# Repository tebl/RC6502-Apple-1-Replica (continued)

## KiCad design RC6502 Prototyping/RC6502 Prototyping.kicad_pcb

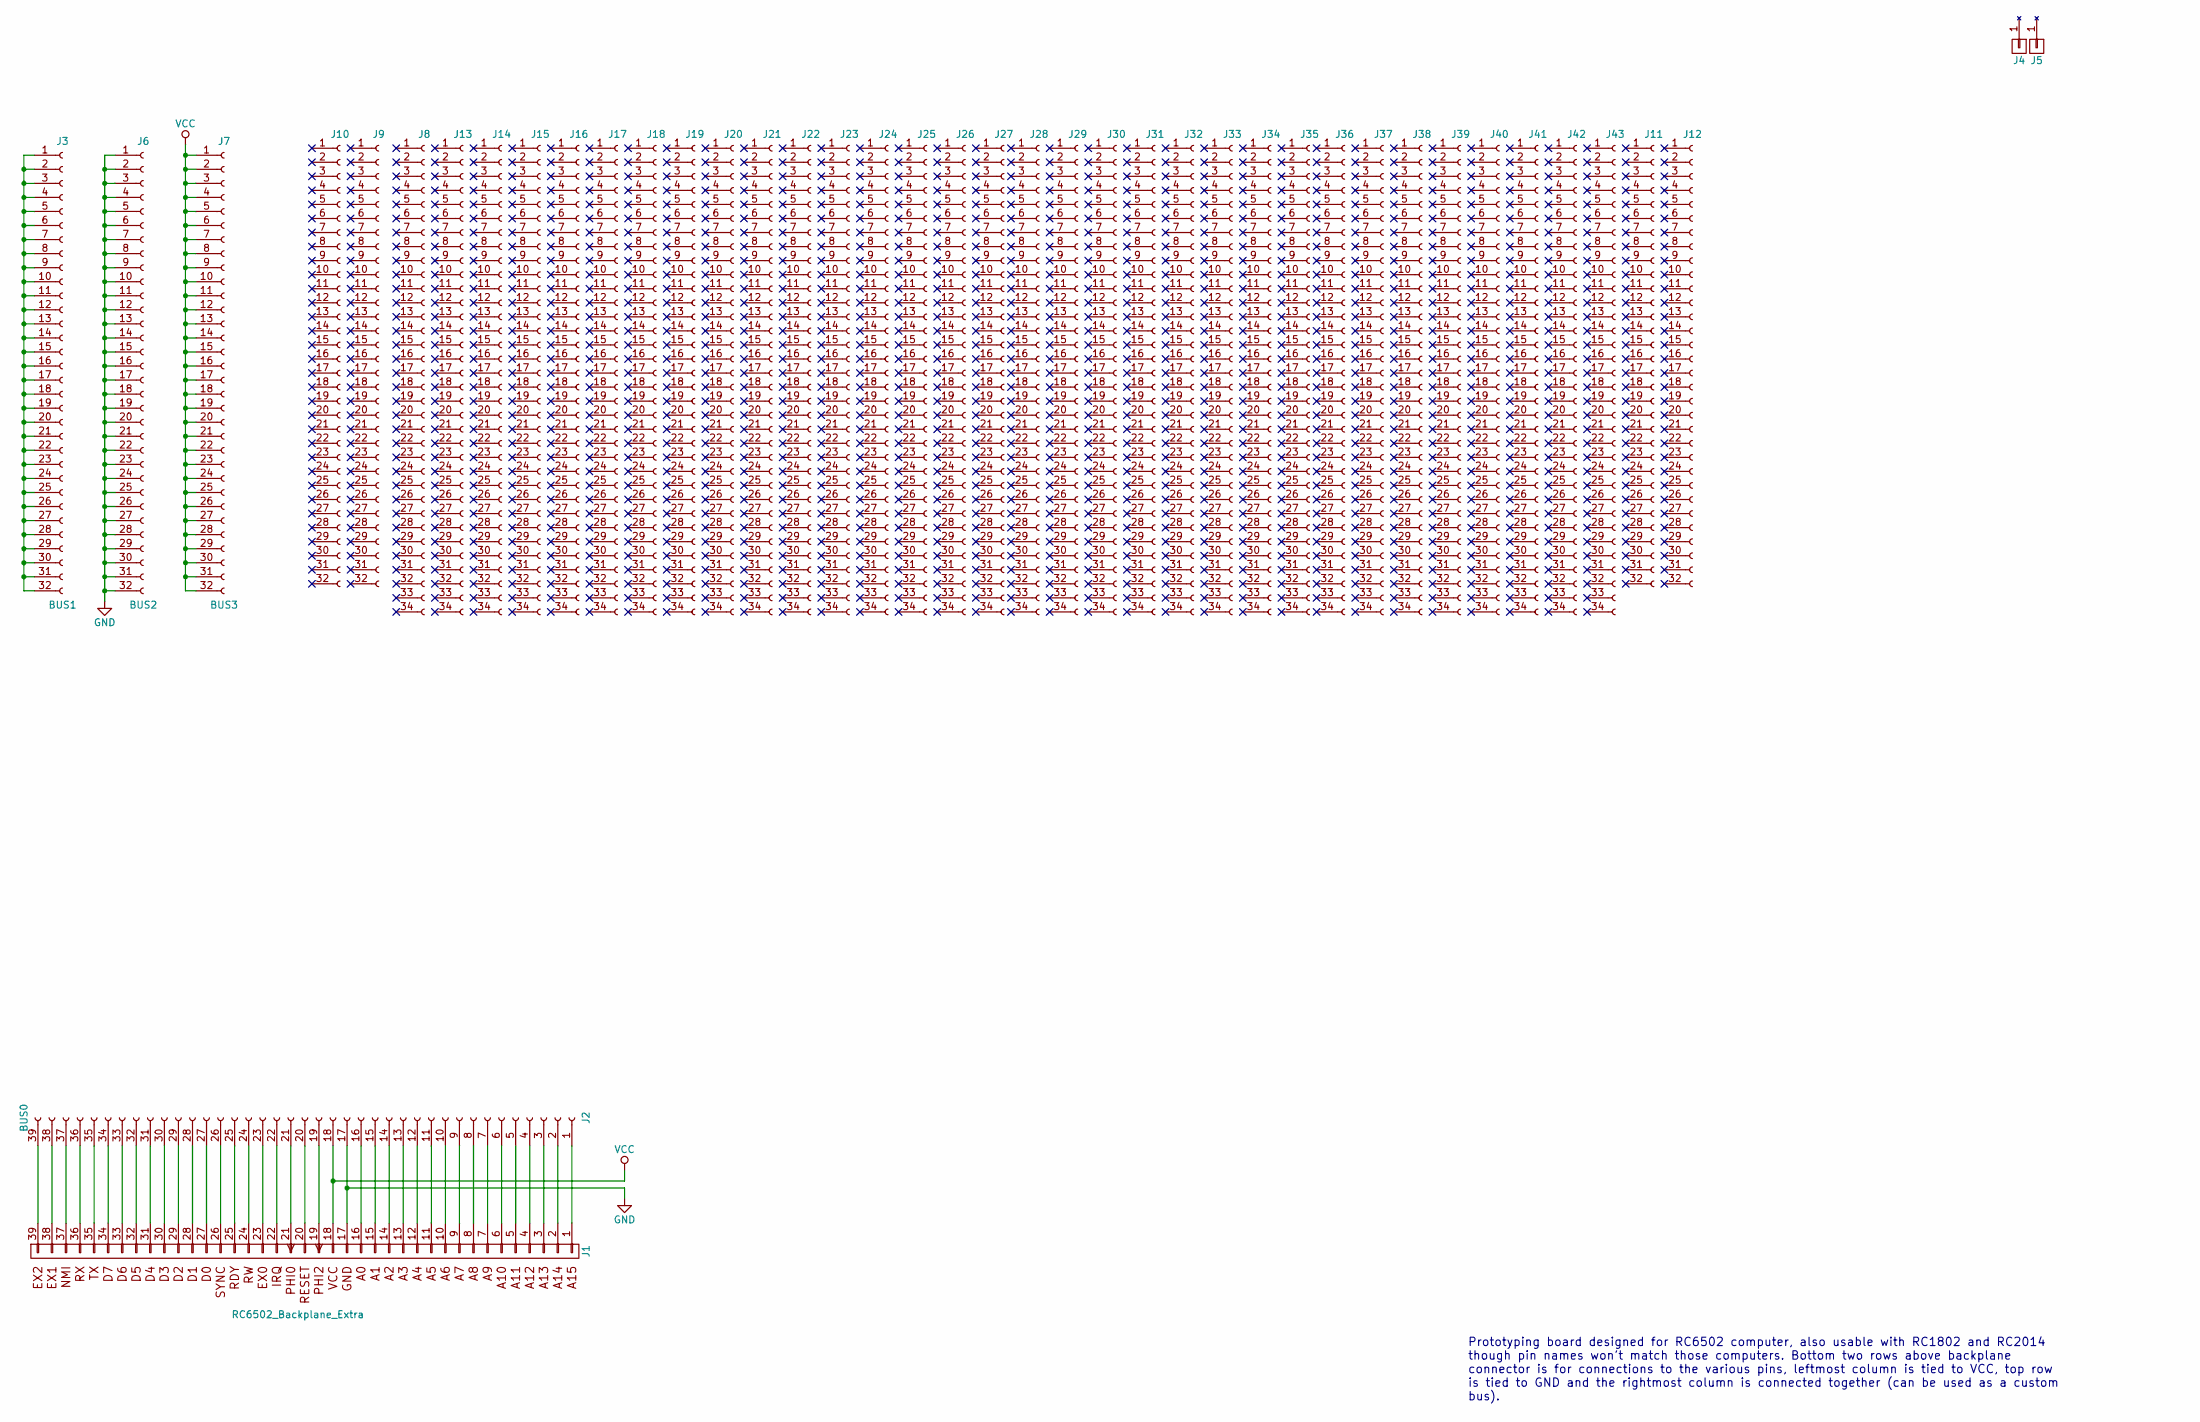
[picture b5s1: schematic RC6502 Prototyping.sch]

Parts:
J1: RC6502_Backplane_Extra; Pin_Header_Angled_1x39_Pitch2.54mm
J2: BUS0; Bus
J3: BUS1; Pin_Header_Straight_1x32_Pitch2.54mm
J4, J5: Mounting
J6: BUS2; Pin_Header_Straight_1x32_Pitch2.54mm
J7: BUS3; Pin_Header_Straight_1x32_Pitch2.54mm
J8, J13, J14, J15, J16, J17, J18, J19, J20, J21, J22, J23, J24, J25, J26, J27, J28, J29, J30, J31, J32, J33, J34, J35, J36, J37, J38, J39, J40, J41, J42, J43: Conn_01x34_Female; 34
J9, J10, J11, J12: Conn_01x32_Female; 32

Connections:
GND: J1.17, J2.17, J6.1, J6.2, J6.3, J6.4, J6.5, J6.6, J6.7, J6.8, J6.9, J6.10, J6.11, J6.12, J6.13, J6.14, J6.15, J6.16, J6.17, J6.18, J6.19, J6.20, J6.21, J6.22, J6.23, J6.24, J6.25, J6.26, J6.27, J6.28, J6.29, J6.30, J6.31, J6.32
unnamed: J1.1 (A15), J2.1
unnamed: J1.2 (A14), J2.2
unnamed: J1.3 (A13), J2.3
unnamed: J1.4 (A12), J2.4
unnamed: J1.5 (A11), J2.5
unnamed: J1.6 (A10), J2.6
unnamed: J1.7 (A9), J2.7
unnamed: J1.8 (A8), J2.8
unnamed: J1.9 (A7), J2.9
unnamed: J1.10 (A6), J2.10
unnamed: J1.11 (A5), J2.11
unnamed: J1.12 (A4), J2.12
unnamed: J1.13 (A3), J2.13
unnamed: J1.14 (A2), J2.14
unnamed: J1.15 (A1), J2.15
unnamed: J1.16 (A0), J2.16
unnamed: J1.19 (PHI2), J2.19
unnamed: J1.20 (RESET), J2.20
unnamed: J1.21 (PHI0), J2.21
unnamed: J1.22 (IRQ), J2.22
unnamed: J1.23 (EX0), J2.23
unnamed: J1.24 (RW), J2.24
unnamed: J1.25 (READY), J2.25
unnamed: J1.26 (SYNC), J2.26
unnamed: J1.27 (D0), J2.27
unnamed: J1.28 (D1), J2.28
unnamed: J1.29 (D2), J2.29
unnamed: J1.30 (D3), J2.30
unnamed: J1.31 (D4), J2.31
unnamed: J1.32 (D5), J2.32
unnamed: J1.33 (D6), J2.33
unnamed: J1.34 (D7), J2.34
unnamed: J1.35 (TX), J2.35
unnamed: J1.36 (RX), J2.36
unnamed: J1.37 (NMI), J2.37
unnamed: J1.38 (EX1), J2.38
unnamed: J1.39 (EX2), J2.39
unnamed: J3.1, J3.2, J3.3, J3.4, J3.5, J3.6, J3.7, J3.8, J3.9, J3.10, J3.11, J3.12, J3.13, J3.14, J3.15, J3.16, J3.17, J3.18, J3.19, J3.20, J3.21, J3.22, J3.23, J3.24, J3.25, J3.26, J3.27, J3.28, J3.29, J3.30, J3.31, J3.32
VCC: J1.18, J2.18, J7.1, J7.2, J7.3, J7.4, J7.5, J7.6, J7.7, J7.8, J7.9, J7.10, J7.11, J7.12, J7.13, J7.14, J7.15, J7.16, J7.17, J7.18, J7.19, J7.20, J7.21, J7.22, J7.23, J7.24, J7.25, J7.26, J7.27, J7.28, J7.29, J7.30, J7.31, J7.32

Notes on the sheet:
Prototyping board designed for RC6502 computer, also usable with RC1802 and RC2014 though pin names won't match those computers. Bottom two rows above backplane connector is for connections to the various pins, leftmost column is tied to VCC, top row is tied to GND and the rightmost column is conne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

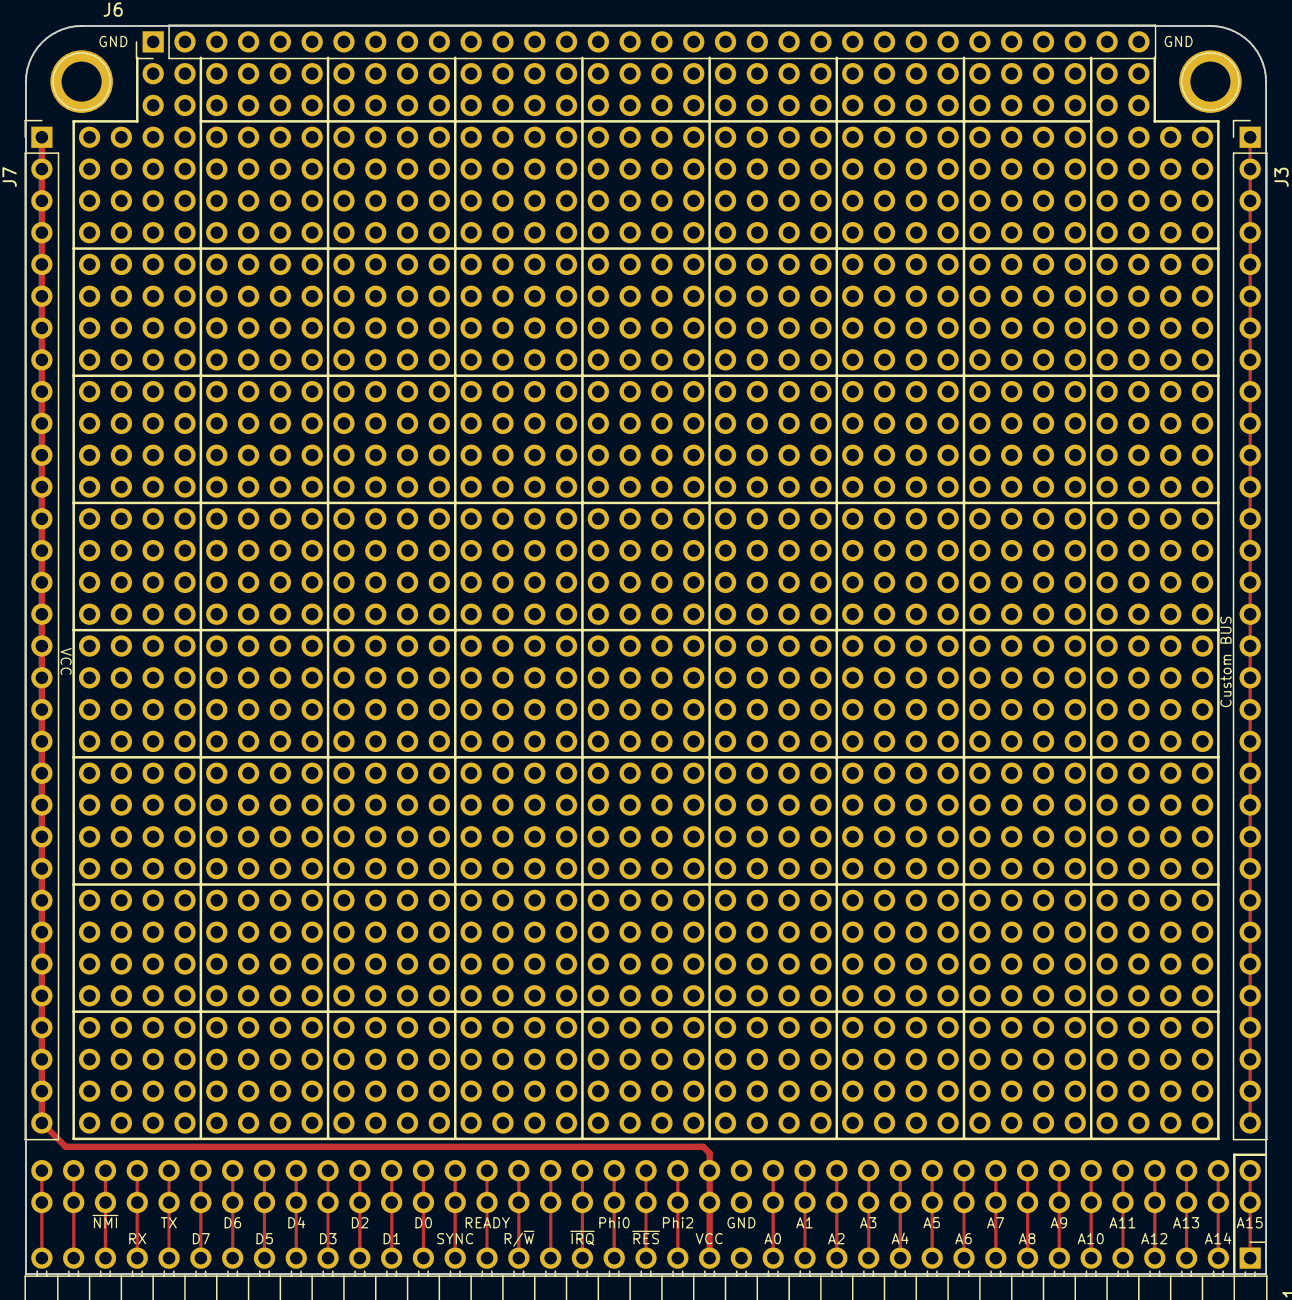
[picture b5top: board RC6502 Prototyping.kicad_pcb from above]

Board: 2 copper layers, 99.1 x 99.7 mm, 43 parts (0 on the bottom side), 40 nets.

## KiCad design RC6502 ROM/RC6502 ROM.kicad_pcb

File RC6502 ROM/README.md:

# RC6502 ROM

The original Apple 1 computer only came with 256 bytes of ROM (Read Only Memory), the bulk of this taken up by the included machine monitor later dubbed WozMon. The machine monitor in itself was written by Wozniak himself by manually entering the data corresponding to the various 6502 instructions and operands byte by byte, mainly because he did not have a computer and the software available to even write assembly level code! An amazing performance by todays standards, though not entirely unheard of in those days since most software was only available for equipment most couldn't even get access to. The Apple 1 was often used with a BASIC variant called "Integer Basic" as a programming language and means of interacting with the machine, but that originally had to be loaded into RAM first via input devices such as tape. The computers original memory map originally looked like the following (picture from Tom Owads Apple 1 Replica book):

.PNG)

The RC6502 computer makes the same changes to the hardware dealing with ROM as was details in the previously mentioned book, the updated memory map looks identical to the one included below (note that any optional modules are not included here). While we initially can see that the blue areas have shifted, this is RAM and we now have an entire 32KB of it as compared to the original - originally we had two blocks of 4KB positioned at the start and at $E000. The modified map changes this second block into ROM, meaning that BASIC is always available to the user, even leaving enough space for at few more utilities!

.PNG)

The implementation of the ROM module answers to addresses from $E000 to $FFFF, in other words the last 8KB of the 6502s 64KB total addressable memory space. The onboard socket takes an EPROM/EEPROM with sizes from 64Kb (27C64/28C64) to 256Kb (27C256/28C256), the latter size giving you the option of using up to four switchable combinations (using A13/14 jumpers). When using the smaller size, these two jumpers should be left unjumpered as the corresponding address pins whould be designated NC (No Connect) on the chips themselves!

**NB!** Note that the redesigned RAM module now supports ROM chips on the same card, so if you do not intend to use the optional paging feature you may want to consider using the new RAM module instead (normally you'd get 5-10 per order anyway)! Note that this might come at an increased cost since the new RAM module requires more ICs to function, but these should be cheap as chips (the potato kind) anyway!

## Optional feature
The board enables the use of backplane pin number 39 for paging purposes, this in essence means the ability to shut of the ROM module using appropriate hardware for controlling this pin. This would enable the computer to regain this section of memory space for other purposes afterwards, possibly by switching it out for more RAM... In most cases this will not be needed, so instead I encourage you to solder a hard links between pads 2 and 3 on JP5 - U2 can also be left off the board.

## Software
As previously mentioned, the supplied binary file (in the [firmware](https://github.com/tebl/RC6502-Apple-1-Replica/tree/master/RC6502%20ROM/firmware)-directory) includes around 8KB of software. The easiest way to get that software onto the selected ROM IC is by using an EPROM programmer, personally I use the MiniPro TL866A and while cheap compared to the alternatives I've found it handles just about anything I've thrown at it.

The following overview is also printed on the back of the SBC silkscreen, while not inherently clear is that the command given is what you would type into the machine monitor program (WozMon) to start the program at the given address. From using the computer and reading the books from the corresponding era you'll want to be spending a lot of your time in BASIC, but when debugging hardware I find WozMon to be the easiest environment to work within. A somewhat detailed guide to the computer can be found by reading the original [operation manual](https://archive.org/details/Apple1Manual1976) from 1976, but the is also a really good guide for the monitor on [https://www.sbprojects.net/projects/apple1/wozmon.php](https://www.sbprojects.net/projects/apple1/wozmon.php).

| Program            | Command |
|--------------------|---------|
| Integer Basic      | $E000 R |
| Krusader Assembler | $F000 R |
| WozMon             | $FF00 R |

# Schematic
The supplied KiCad files should be sufficient as both a schematic and as a starting
point for ordering PCBs, the schematic is also available in
[PDF-format](https://github.com/tebl/RC6502-Apple-1-Replica/raw/master/RC6502%20ROM/export/RC6502%20ROM.pdf). You can refer to the BOM below for a list of suggested components to use, part numbers in parenthesis are optional and is not required.

# BOM
These are the components needed to put together your very own ROM-module for the RC6502 computer, should be able to get all of this from your favourite parts supplier through your favourite local parts supplier. For the pin headers, both male and female - if you can't find the exact pin count, just buy the longer versions and snip/cut off the parts you don't need (get extra in case of accidents, and don't cut yourself either!). Part counts in parenthesis are to be considered optional, so if you don't have any plans for them - then they can probably be left out until you need them.

| Reference | Item                                  | Count  |
| --------- | ------------------------------------- | ------ |
| PCB       | Fabricate yourself using KiCad files  |     1  |
| U1        | 27C64, 28C64, 27C256 or 28C256        |     1  |
| U2        | 74LS00 DIP                            |     1  |
| U3        | 74LS00 DIP                            |   (1)  |
| C1-C3     | 100nF ceramic capacitor               |     3  |
| R1        | 10K Ohm resistor                      |   (1)  |
| J1        | 1x39 right angle pin header, male     |     1  |
| JP1,JP3   | 1x3 straight pin header, male         |     2  |
| JP3,JP4   | 1x3 straight pin header, male         |   (2)  |
| JP5       | Piece of wire                         |     1  |
| JP1,JP3   | 1x3 straight pin header, male         |     1  |
|           | Jumper caps                           | 2 (2)  |

If you would like to have a copy of one or more modules, what you'll need to do is zip up the contents of the export directory for each module and give that to your favourite PCB fabrication plant. Personally I prefer to use [PCBWay](https://www.pcbway.com/setinvite.aspx?inviteid=88707), each module has been designed to fit inside the 5$ dimensions. Use the link provided when signing up to support this project!

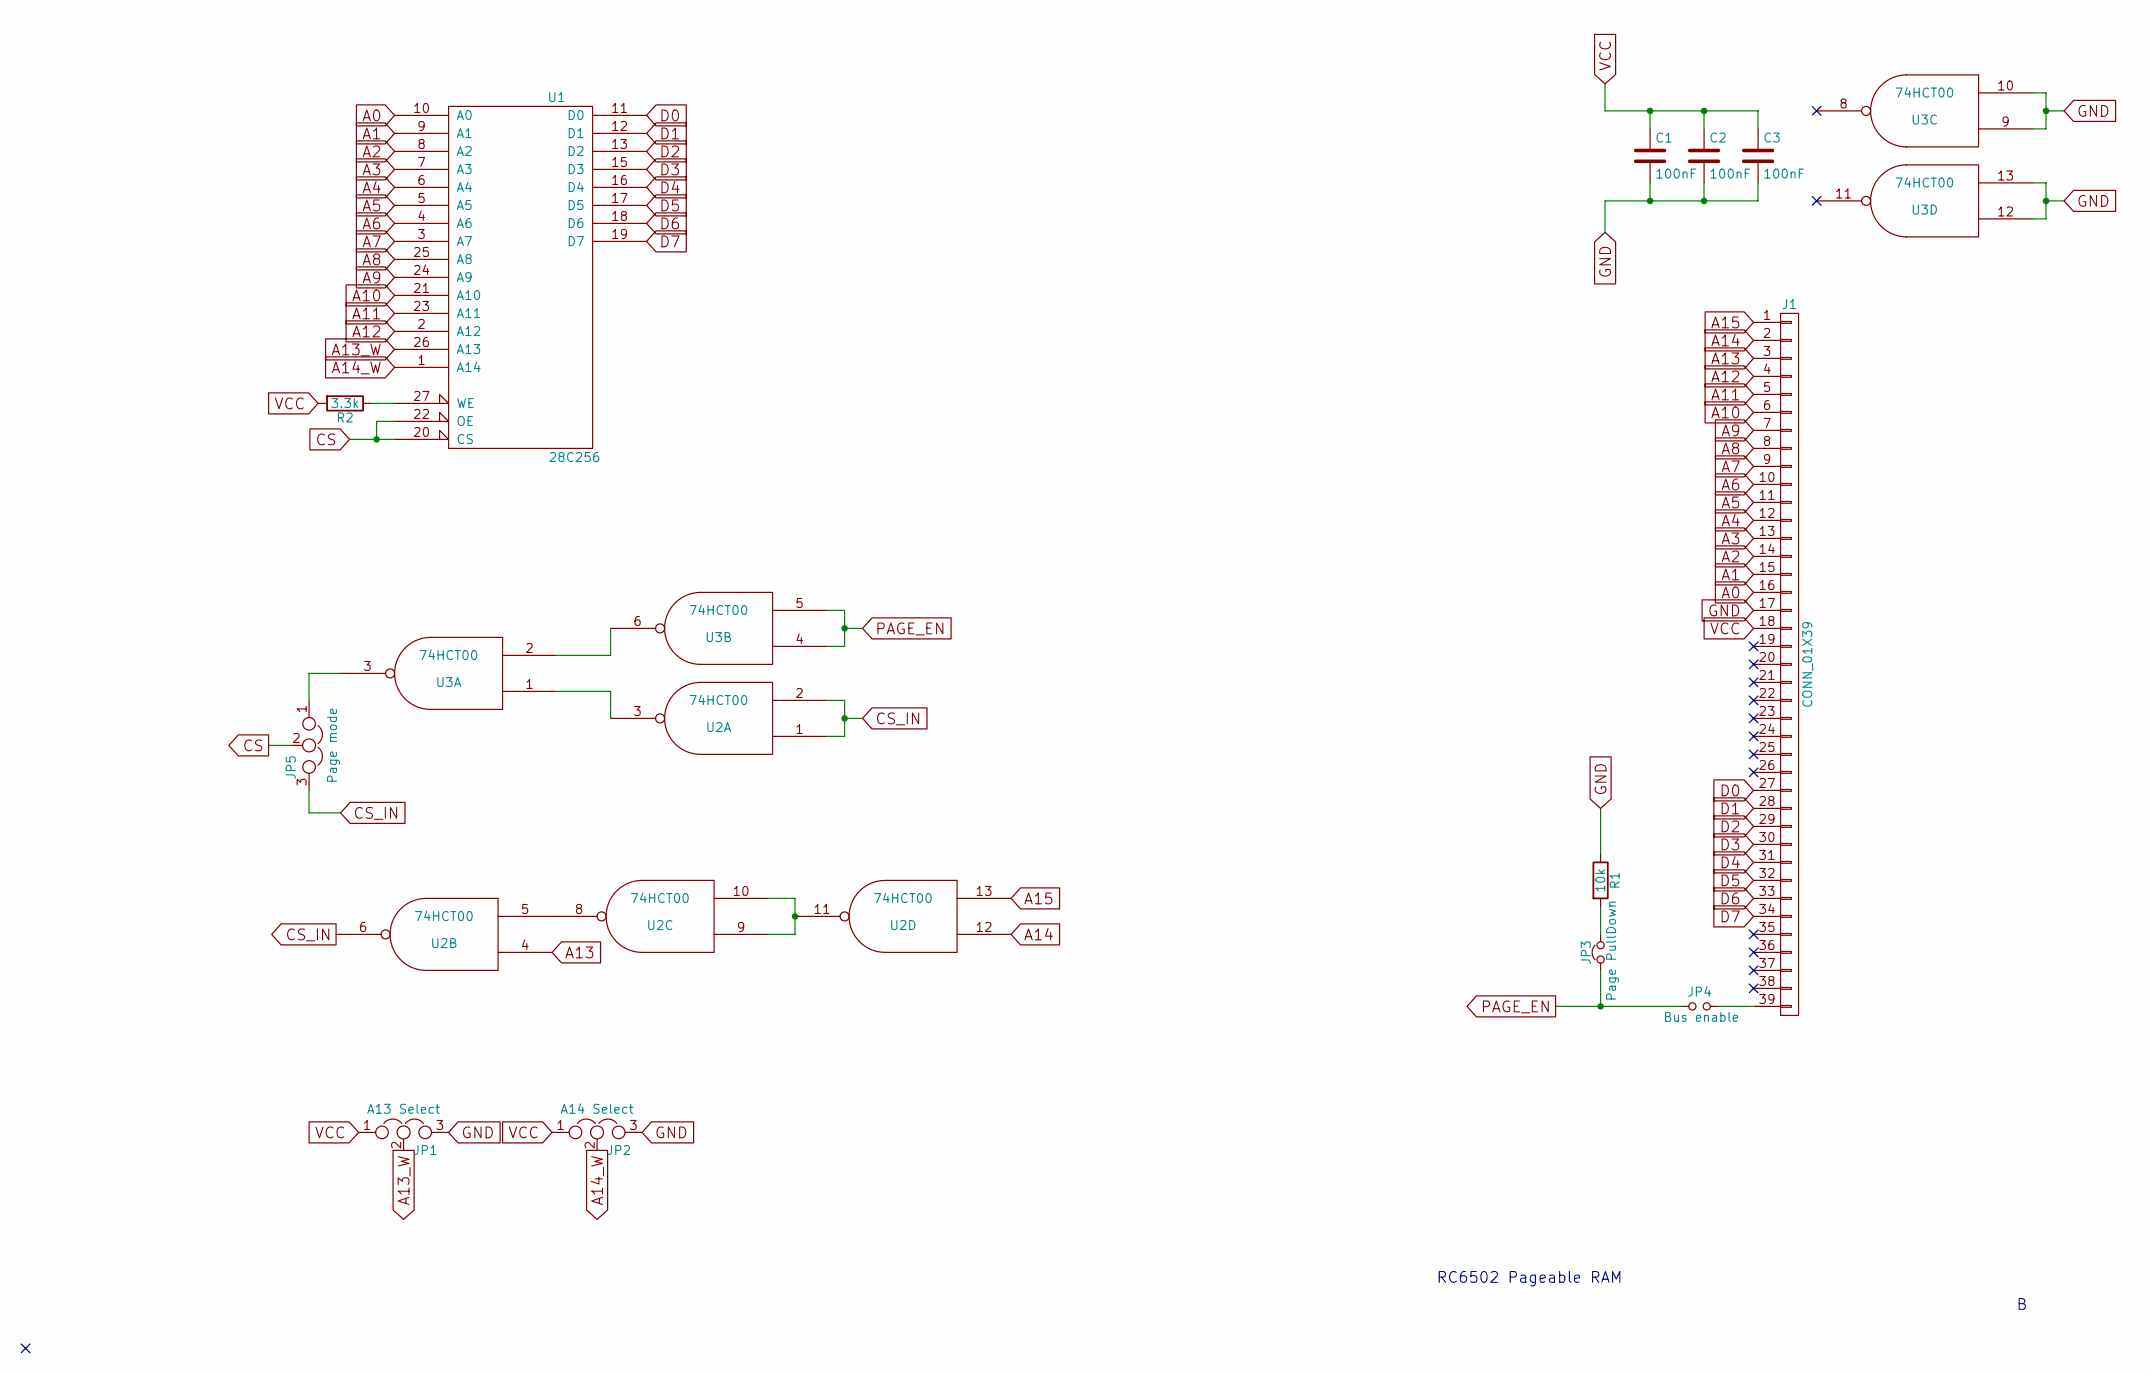
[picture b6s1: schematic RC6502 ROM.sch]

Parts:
C1, C2, C3: 100nF; C_Disc_D4.7mm_W2.5mm_P5.00mm
J1: CONN_01X39; Pin_Header_Angled_1x39_Pitch2.54mm
JP1: A13 Select; Pin_Header_Straight_1x03_Pitch2.54mm
JP2: A14 Select; Pin_Header_Straight_1x03_Pitch2.54mm
JP3: Page PullDown; Pin_Header_Angled_1x02_Pitch2.54mm
JP4: Bus enable; Pin_Header_Angled_1x02_Pitch2.54mm
JP5: Page mode; Pin_Header_Straight_1x03_Pitch2.54mm
R1: 10k; R_Axial_DIN0207_L6.3mm_D2.5mm_P10.16mm_Horizontal
R2: 3.3k; R_Axial_DIN0207_L6.3mm_D2.5mm_P10.16mm_Horizontal
U1: 28C256; DIP-28_W15.24mm_Socket_LongPads
U2, U3: 74HCT00; DIP-14_W7.62mm_Socket

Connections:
A0: J1.16, U1.10 (A0)
A1: J1.15, U1.9 (A1)
A2: J1.14, U1.8 (A2)
A3: J1.13, U1.7 (A3)
A4: J1.12, U1.6 (A4)
A5: J1.11, U1.5 (A5)
A6: J1.10, U1.4 (A6)
A7: J1.9, U1.3 (A7)
A8: J1.8, U1.25 (A8)
A9: J1.7, U1.24 (A9)
A10: J1.6, U1.21 (A10)
A11: J1.5, U1.23 (A11)
A12: J1.4, U1.2 (A12)
A13: J1.3, U2.4
A13_W: JP1.2, U1.26 (A13)
A14: J1.2, U2.12
A14_W: JP2.2, U1.1 (A14)
A15: J1.1, U2.13
CS: JP5.2, U1.20 (CS), U1.22 (OE)
CS_IN: JP5.3, U2.1, U2.2, U2.6
D0: J1.27, U1.11 (D0)
D1: J1.28, U1.12 (D1)
D2: J1.29, U1.13 (D2)
D3: J1.30, U1.15 (D3)
D4: J1.31, U1.16 (D4)
D5: J1.32, U1.17 (D5)
D6: J1.33, U1.18 (D6)
D7: J1.34, U1.19 (D7)
GND: C1.2, C2.2, C3.2, J1.17, JP1.3, JP2.3, R1.1, U1.14 (GND), U2.7 (GND), U3.7 (GND), U3.9, U3.10, U3.12, U3.13
unnamed: J1.39, JP4.2
unnamed: JP3.2, R1.2
unnamed: JP5.1, U3.3
unnamed: R2.1, U1.27 (WE)
unnamed: U2.3, U3.1
unnamed: U2.5, U2.8
unnamed: U2.9, U2.10, U2.11
unnamed: U3.2, U3.6
PAGE_EN: JP3.1, JP4.1, U3.4, U3.5
VCC: C1.1, C2.1, C3.1, J1.18, JP1.1, JP2.1, R2.2, U1.28 (VCC), U2.14 (VCC), U3.14 (VCC)

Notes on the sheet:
RC6502 Pageable RAM

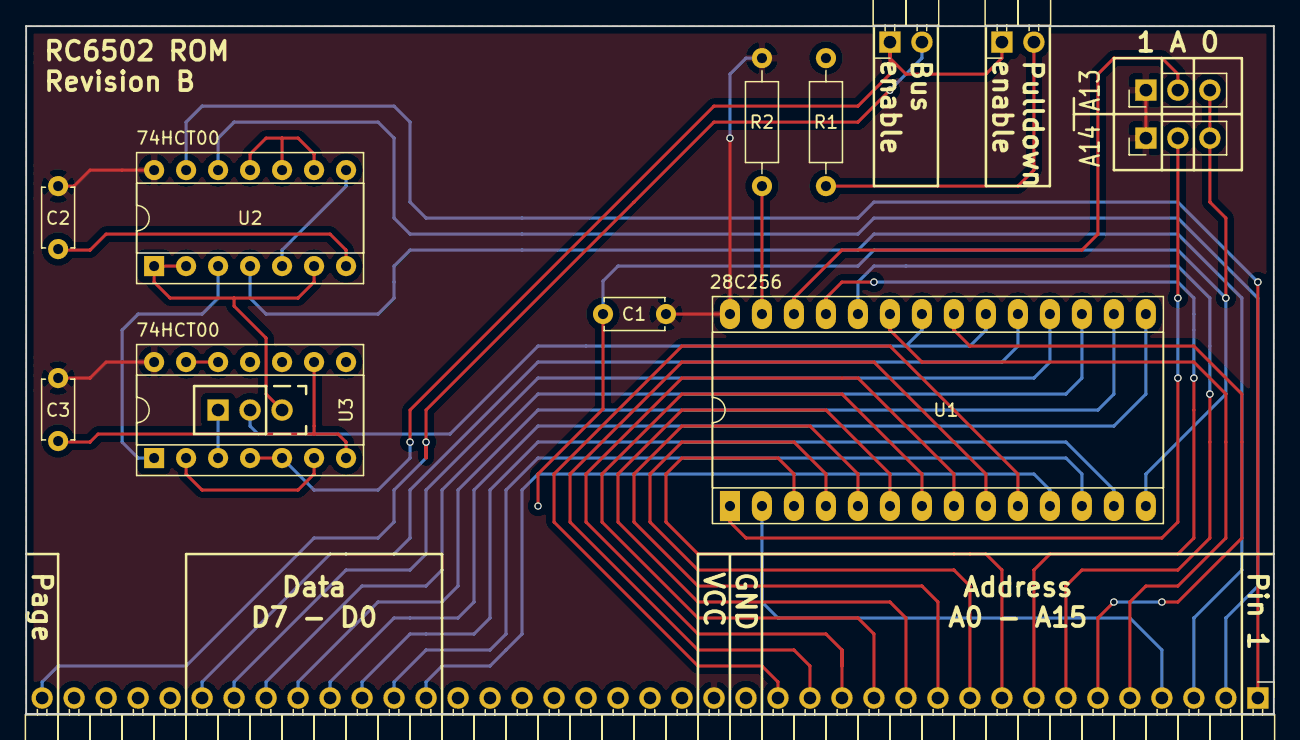
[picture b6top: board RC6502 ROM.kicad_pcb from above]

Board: 2 copper layers, 99.1 x 54.6 mm, 14 parts (1 on the bottom side), 39 nets.

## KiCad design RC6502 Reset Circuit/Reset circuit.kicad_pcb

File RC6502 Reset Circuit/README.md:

# RC6502 Reset Circuit

Funny story, the original Apple 1 computer did not have a power-on reset circuit! While this was actually quite common for computers from that time, it meant that the circuitry would often start up in an unknown state... fancy way of saying that internal CPU registers and memory would be filled with seemingly random date. The user would then have to manually push the reset button, this worked most of the time... Why? Because the 6502 is a particularly special little CPU that, it has very specific timing requirements for all of this to work properly. So I took a book from the Commodore 64 manual and used that, no need to reinvent wheels already invented by other far more [gifted people](https://www.grappendorf.net/projects/6502-home-computer/reset-circuit.html)!

In addition to power-on reset and normal reset functionality, this module also takes care of handling the system clock by including a footprint for a 5v TTL crystal oscillator. While you can use a standard 1Mhz oscillator, there are 2Mhz capable CPUs normally labelled 6502A so in many ways it make sense to install a 2Mhz oscillator and then jumper J2 for a /2 (pins 5-6) clock division for standard 1Mhz CPUs. Jumper positions 3-4 if installing 1Mhz oscillator. Note that the [CPU](https://github.com/tebl/RC6502/tree/master/RC6502%20CPU)-module also includes a footprint for an oscillator, disable that and then jumper J2 pins 1-2 to enable the one on this board. If you have plans of using several CPU boards with varying speeds so that you can easily swap between them, then it would make sense to only use the oscillators installed on the CPU module themselves.

Picture below shows the first revision of the board, note that this does not include the functionality for setting up a clock divider.

# Schematic
The supplied KiCad files should be sufficient as both a schematic and as a starting
point for ordering PCBs, the schematic is also available in
[PDF-format](https://github.com/tebl/RC6502-Apple-1-Replica/tree/master/RC6502%20Reset%20Circuit). You can refer to the BOM below for a list of suggested components to use, part numbers in parenthesis are optional and is not required.

# BOM
These are the components needed to put together your very own Reset Circuit-module for the RC6502 computer, all of which you should be able to get from your favourite parts supplier through your favourite electronic parts supplier though the oscillator TTL oscillator might require a well-stocked one. For the pin headers, both male and female - if you can't find the exact pin count, just buy the longer versions and snip/cut off the parts you don't need (get extra in case of accidents, and don't cut yourself either!). As previously mentioned, part counts in parenthesis are to be considered optional so feel free to leave them out if you don't have any specific plans for them.

| Reference | Item                                  | Count   |
| --------- | ------------------------------------- | ------- |
| PCB       | Fabricate yourself using KiCad files  |      1  |
| C1,C3-C5  | 100nF ceramic capacitor               |      4  |
| C2        | 10uF 16V electrolytic capacitor       |      1  |
| D1        | 5mm LED diode, green or red color     |      1  |
| J1        | 1x39 right angle pin header, male     |      1  |
| J2        | 2x4 straight pin header, male         |      3  |
| R1        | 1M ohm resistor                       |      1  |
| R2        | 47k ohm resistor                      |      1  |
| R3        | 1k ohm resistor                       |      1  |
| R4        | 330 ohm resistor                      |      1  |
| SW1       | Momentary push button                 |      1  |
| U1        | NE555 DIP                             |      1  |
| U2        | 74LS04 DIP                            |      1  |
| U3        | 74LS74 DIP                            |     (1) |
| X1        | 1.000Mhz TTL Oscillator, (DIP 14)     |     (1) |
|           | Jumper caps                           |      2  |

If you would like to have a copy of one or more modules, what you'll need to do is zip up the contents of the export directory for each module and give that to your favourite PCB fabrication plant. Personally I prefer to use [PCBWay](https://www.pcbway.com/setinvite.aspx?inviteid=88707), each module has been designed to fit inside the 5$ dimensions. Use the link provided when signing up to support this project!

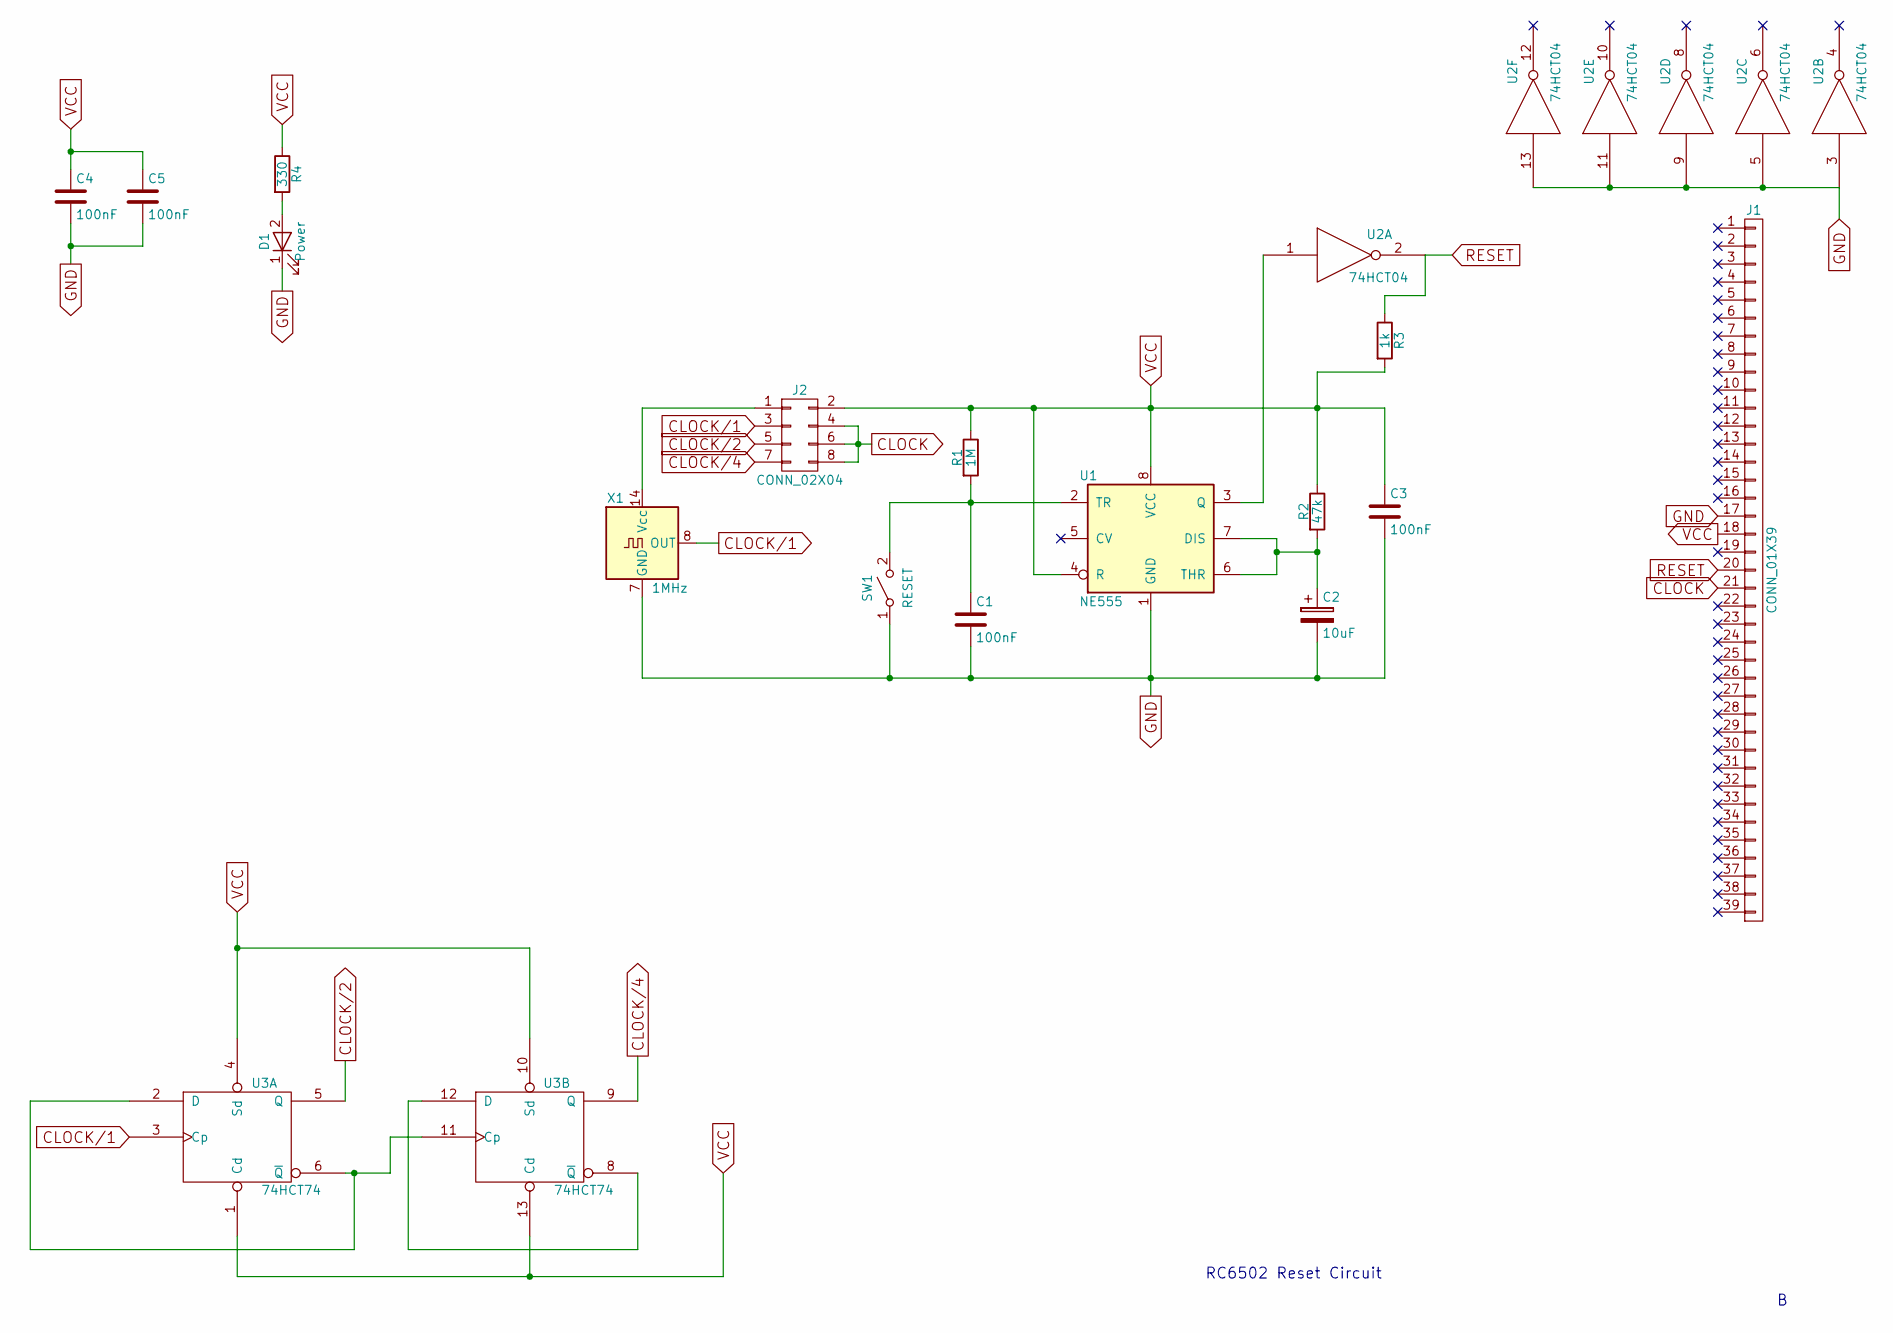
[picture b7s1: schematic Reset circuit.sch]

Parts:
C1, C3, C4, C5: 100nF; C_Disc_D4.7mm_W2.5mm_P5.00mm
C2: 10uF; CP_Radial_D4.0mm_P2.00mm
D1: Power; LED_D5.0mm
J1: CONN_01X39; Pin_Header_Angled_1x39_Pitch2.54mm
J2: CONN_02X04; Pin_Header_Straight_2x04_Pitch2.54mm
R1: 1M; R_Axial_DIN0207_L6.3mm_D2.5mm_P10.16mm_Horizontal
R2: 47k; R_Axial_DIN0207_L6.3mm_D2.5mm_P10.16mm_Horizontal
R3: 1k; R_Axial_DIN0207_L6.3mm_D2.5mm_P10.16mm_Horizontal
R4: 330; R_Axial_DIN0207_L6.3mm_D2.5mm_P10.16mm_Horizontal
SW1: RESET; SW_PUSH_6mm
U1: NE555; DIP-8_W7.62mm
U2: 74HCT04; DIP-14_W7.62mm
U3: 74HCT74; DIP-14_W7.62mm_Socket
X1: 1MHz; Oscillator_DIP-14

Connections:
CLOCK: J1.21, J2.4, J2.6, J2.8
CLOCK/1: J2.3, U3.3 (Cp), X1.8 (OUT)
CLOCK/2: J2.5, U3.5 (Q)
CLOCK/4: J2.7, U3.9 (Q)
GND: C1.2, C2.2, C3.2, C4.2, C5.2, D1.1 (K), J1.17, SW1.1 (A), U1.1 (GND), U2.3, U2.5, U2.7 (GND), U2.9, U2.11, U2.13, U3.7 (GND), X1.7 (GND)
unnamed: C1.1, R1.2, SW1.2 (B), U1.2 (TR)
unnamed: C2.1, R2.2, U1.6 (THR), U1.7 (DIS)
unnamed: D1.2 (A), R4.2
unnamed: J2.1, X1.14 (Vcc)
unnamed: U1.3 (Q), U2.1
unnamed: U3.2 (D), U3.6 (~Q), U3.11 (Cp)
unnamed: U3.8 (~Q), U3.12 (D)
RESET: J1.20, R3.1, U2.2
VCC: C3.1, C4.1, C5.1, J1.18, J2.2, R1.1, R2.1, R3.2, R4.1, U1.4 (R), U1.8 (VCC), U2.14 (VCC), U3.1 (Cd), U3.4 (Sd), U3.10 (Sd), U3.13 (Cd), U3.14 (VCC)

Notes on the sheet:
RC6502 Reset Circuit

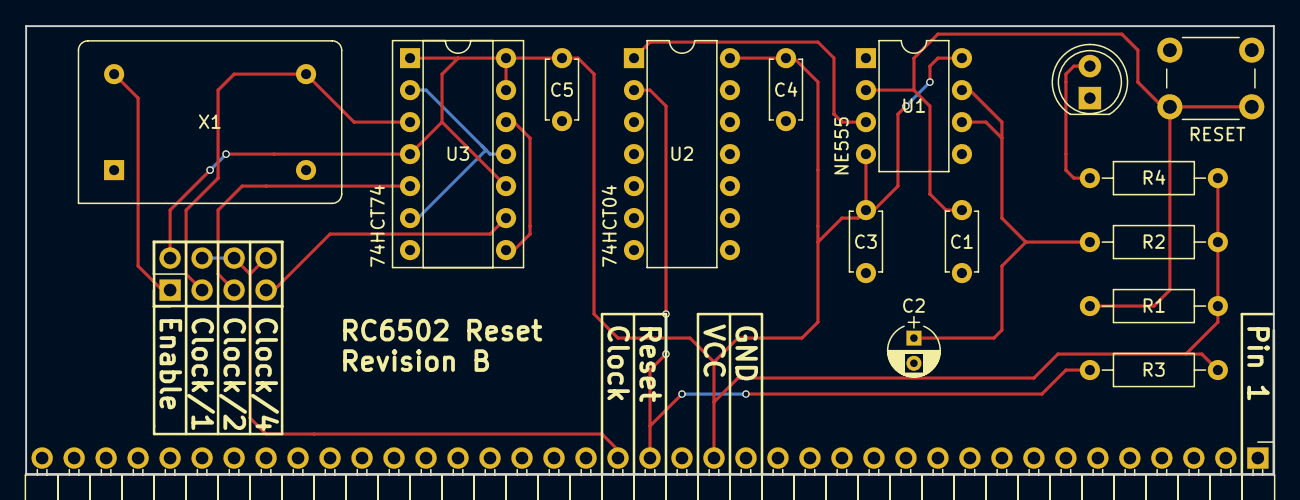
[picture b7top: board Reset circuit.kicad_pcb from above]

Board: 2 copper layers, 99.1 x 35.6 mm, 17 parts (0 on the bottom side), 14 nets.
